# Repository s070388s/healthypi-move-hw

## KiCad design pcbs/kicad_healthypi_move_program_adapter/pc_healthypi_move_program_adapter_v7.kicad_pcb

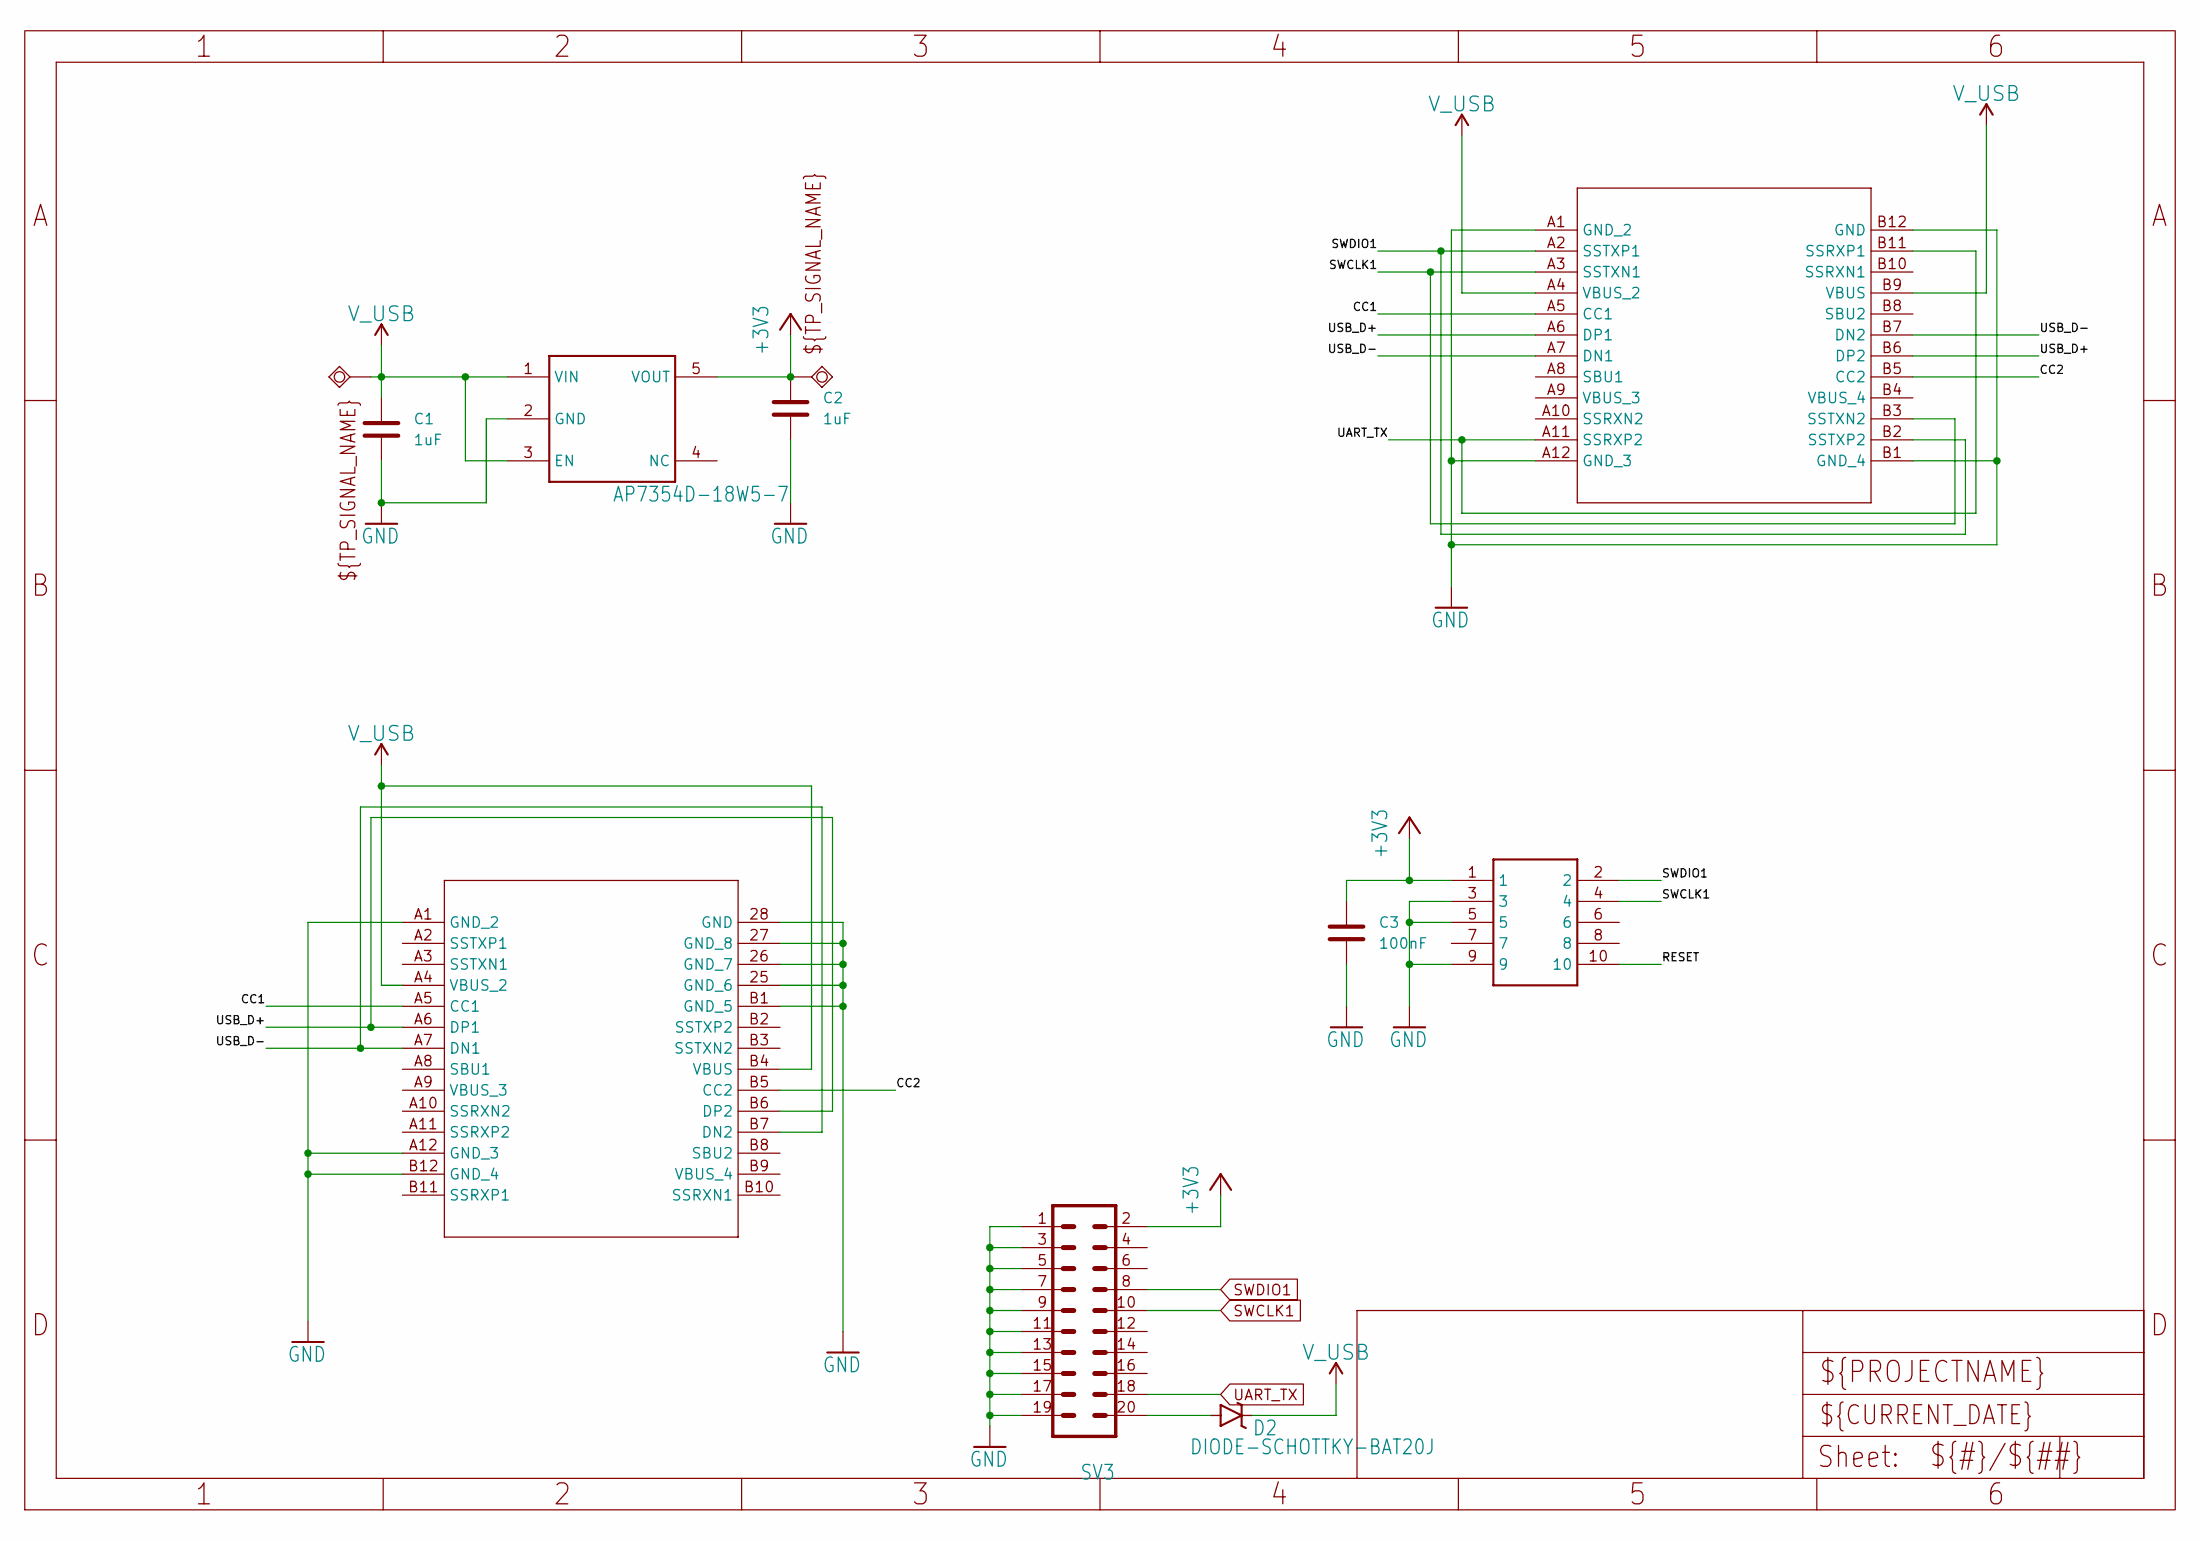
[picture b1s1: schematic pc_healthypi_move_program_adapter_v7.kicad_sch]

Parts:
C1, C2: 1uF; C_0402_1005Metric
C3: 100nF; C_0402_1005Metric
CON_JTAG1: HDR-SMT-50MIL/5X2; HDR-SMT-50MIL_5X2
D2: DIODE-SCHOTTKY-BAT20J; SOD-323
J3: USB4151-GF-C; USB4151-GF-C_GCT
SV3: MA10-2
SWIO1, SWIO5: TPSQTP11R; TP11R
U2: USB4115-03-C; USB4115-03-C_GCT
U$6: AP7354D-18W5-7; SOT95P285X140-5N

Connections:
+3V3: C2.1, C3.1, CON_JTAG1.1, SV3.2, SWIO5.TP, U$6.5 (VOUT)
/CC1: J3.A5 (CC1), U2.A5 (CC1)
/CC2: J3.B5 (CC2), U2.B5 (CC2)
/RESET: CON_JTAG1.10
/USB_D+: J3.A6 (DP1), J3.B6 (DP2), U2.A6 (DP1), U2.B6 (DP2)
/USB_D-: J3.A7 (DN1), J3.B7 (DN2), U2.A7 (DN1), U2.B7 (DN2)
GND: C1.2, C2.2, C3.2, CON_JTAG1.3, CON_JTAG1.5, CON_JTAG1.9, J3.A1 (GND_2), J3.A12 (GND_3), J3.B1 (GND_4), J3.B12 (GND), SV3.1, SV3.3, SV3.5, SV3.7, SV3.9, SV3.11, SV3.13, SV3.15, SV3.17, SV3.19, U2.25 (GND_6), U2.26 (GND_7), U2.27 (GND_8), U2.28 (GND), U2.A1 (GND_2), U2.A12 (GND_3), U2.B1 (GND_5), U2.B12 (GND_4), U$6.2 (GND)
unnamed: D2.A, SV3.20
SWCLK1: CON_JTAG1.4, J3.A3 (SSTXN1), J3.B3 (SSTXN2), SV3.10
SWDIO1: CON_JTAG1.2, J3.A2 (SSTXP1), J3.B2 (SSTXP2), SV3.8
UART_TX: J3.A11 (SSRXP2), J3.B11 (SSRXP1), SV3.18
V_USB: C1.1, D2.C, J3.A4 (VBUS_2), J3.B9 (VBUS), SWIO1.TP, U2.A4 (VBUS_2), U2.B4 (VBUS), U$6.1 (VIN), U$6.3 (EN)

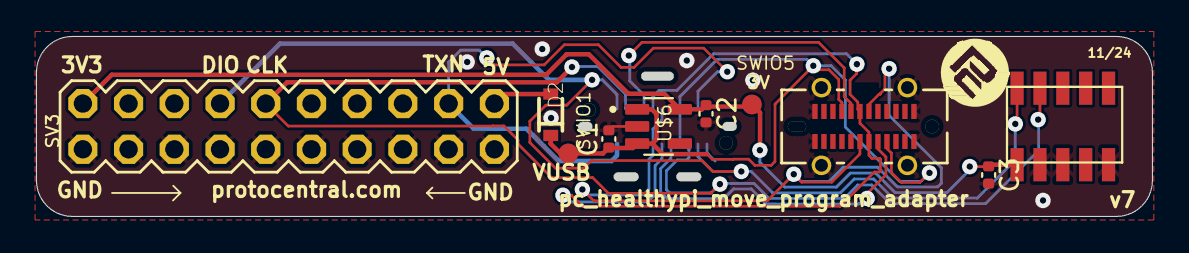
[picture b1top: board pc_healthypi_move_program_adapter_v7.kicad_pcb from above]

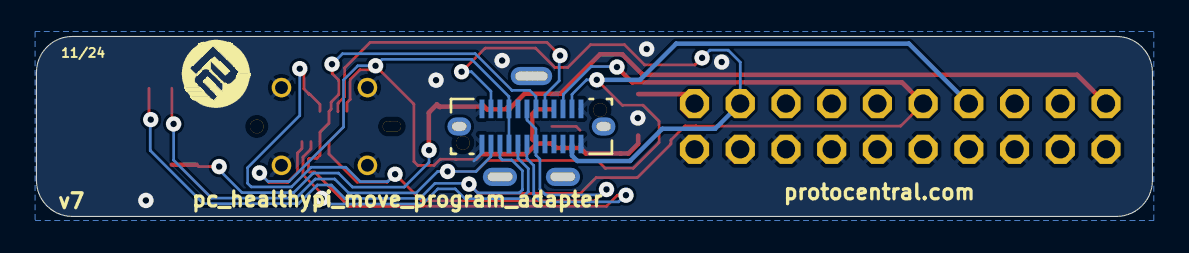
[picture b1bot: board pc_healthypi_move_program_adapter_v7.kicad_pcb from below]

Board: 4 copper layers, 61.5 x 9.5 mm, 13 parts (2 on the bottom side), 11 nets.

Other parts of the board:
U$2, U$3: PCROUNDLOGO

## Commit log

2025-12-15 Add latest enclosure models and PCB designs
